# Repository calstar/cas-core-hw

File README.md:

# cas-core-hw
Common Avionics Stack - Core Module - Hardware

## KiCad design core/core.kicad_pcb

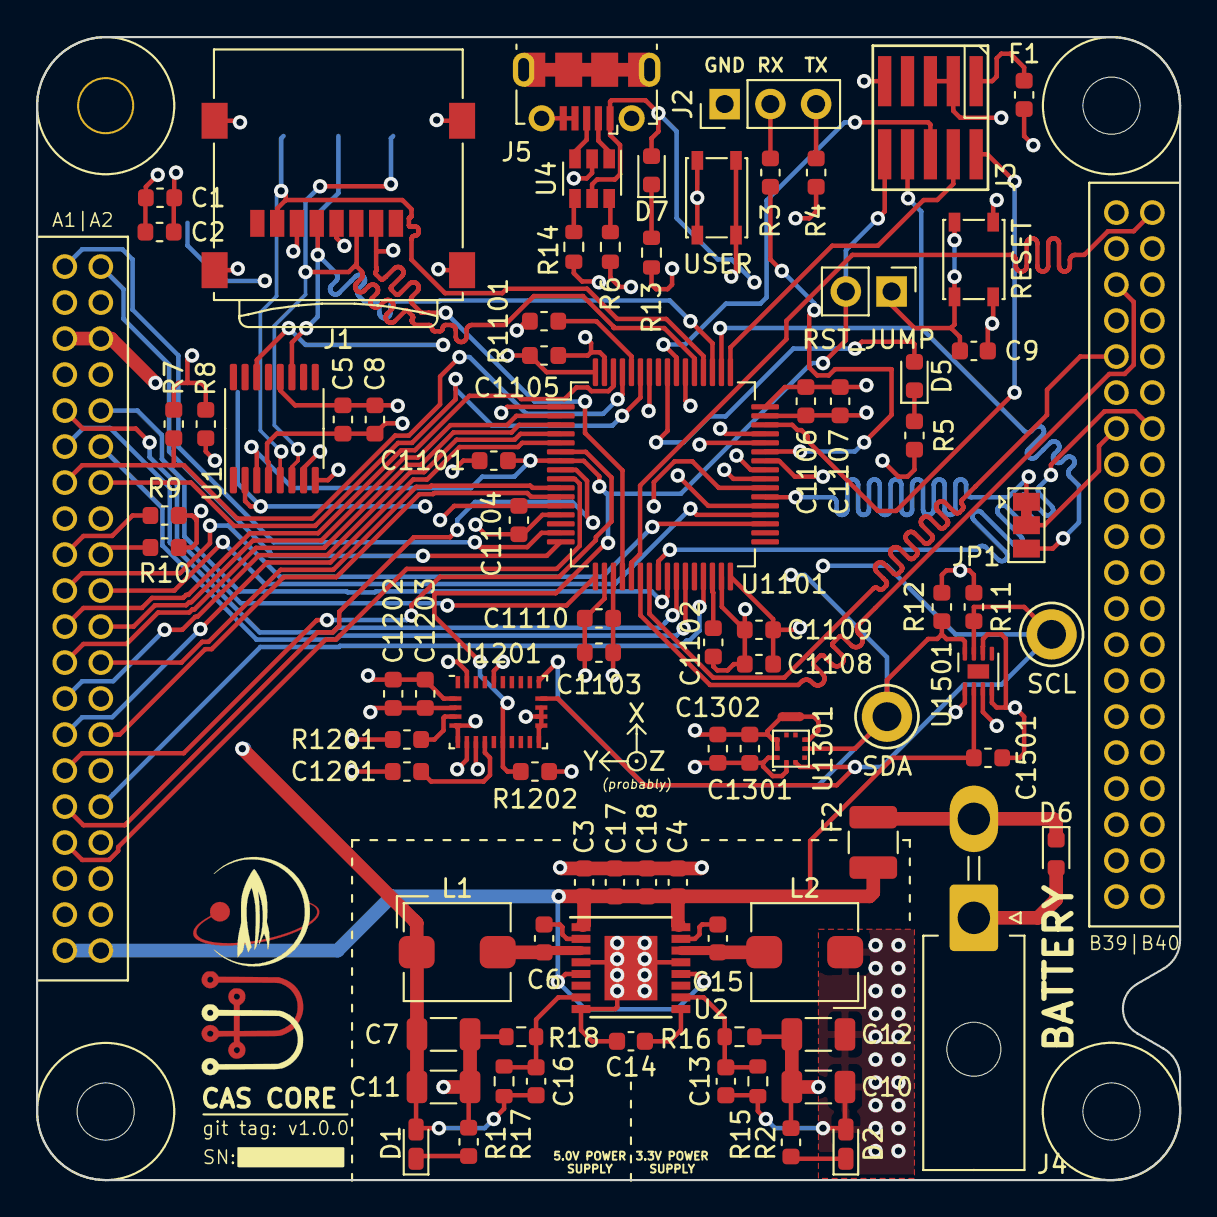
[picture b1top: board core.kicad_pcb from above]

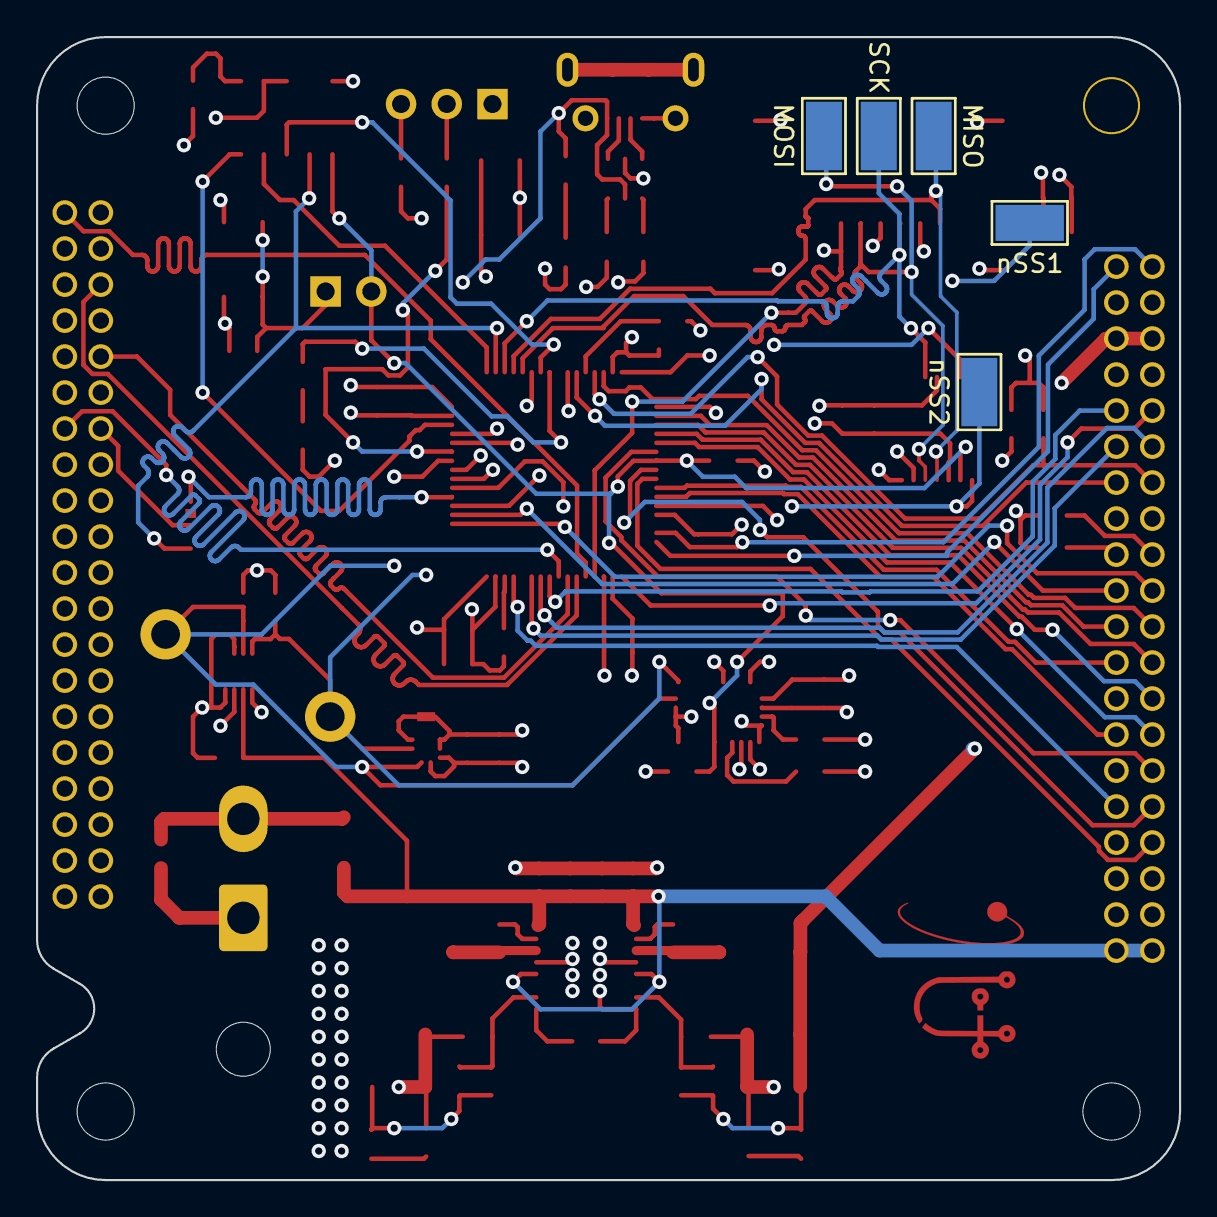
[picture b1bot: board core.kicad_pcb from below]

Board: 4 copper layers, 63.5 x 63.5 mm, 91 parts (5 on the bottom side), 78 nets.

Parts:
C1, C3, C4, C5, C1103: 10u; C_0603_1608Metric
C2, C6, C8, C9, C15: 100n; C_0603_1608Metric
C7, C10, C11, C12: 22u; C_1206_3216Metric
C13, C16: 10p; C_0603_1608Metric
C14, C1107: 1u; C_0603_1608Metric
C17, C18, C1101, C1104, C1105, C1106, C1108, C1109, C1110, C1501: 0.1u; C_0603_1608Metric
C1102: 4.7u; C_0603_1608Metric
C1201: 1uF; C_0603_1608Metric
C1202: 120nF; C_0603_1608Metric
C1203, C1301, C1302: 100nF; C_0603_1608Metric
D1, D2: LED; LED_0603_1608Metric_Castellated
D5, D7: LED; LED_0603_1608Metric
D6: 40V; D_0603_1608Metric
F1: Fuse_Small; Fuse_0603_1608Metric
F2: CHONK; Fuse_1210_3225Metric
H1: STAR; star_fancy
H2: BAC; bac
J1: Micro_SD_Card; microSD_HC_Wuerth_693072010801
J2: UART_DEBUG; PinHeader_1x03_P2.54mm_Vertical
J3: Conn_ARM_JTAG_SWD_10; FTSH-105-01-L-DV-K
J4: Conn_01x02; Molex_Mini-Fit_Jr_5569-02A2_2x01_P4.20mm_Horizontal
J5: USB_OTG; USB_Micro-B_Molex-105017-0001
J1001: CAS_stacking; CAS_physical
JP1: Jumper_3_Bridged12; SolderJumper-3_P1.3mm_Bridged12_Pad1.0x1.5mm
JP2: RST_JUMP; PinHeader_1x02_P2.54mm_Vertical
L1: 4.7u; L_Bourns_SRP5030T
L2: 2.2u; L_Bourns_SRP5030T
NT1301: Net-Tie_2; NetTie-2_SMD_Pad0.5mm
R1, R2, R5, R13: 1k; R_0603_1608Metric
R3, R4: 330; R_0603_1608Metric
R6, R14: 20; R_0603_1608Metric
R7, R8, R9, R10, R11, R12: 4.7k; R_0603_1608Metric
R15: 73.2k; R_0603_1608Metric
R16, R18: 22.1k; R_0603_1608Metric
R17: 124k; R_0603_1608Metric
R1101: 10K; R_0603_1608Metric
R1201, R1202: 10k; R_0603_1608Metric
SW1: RESET; SW_SPST_PTS810
SW2: USER; SW_SPST_PTS810
TP2: MISO; TestPoint_Keystone_5019_Minature
TP3: SCK; TestPoint_Keystone_5019_Minature
TP4: nSS2; TestPoint_Keystone_5019_Minature
TP6: SDA; TestPoint_Keystone_5010-5014_Multipurpose
TP8: MOSI; TestPoint_Keystone_5019_Minature
TP9: nSS1; TestPoint_Keystone_5019_Minature
TP12: SCL; TestPoint_Keystone_5010-5014_Multipurpose
U1: SC18IS600; TSSOP-16_4.4x5mm_P0.65mm
U2: TPS54X94; TSSOP-16-1EP_4.4x5mm_P0.65mm
U4: USBLC6-2SC6; SOT-23-6
U1101: STM32F401RETx; LQFP-64_10x10mm_P0.5mm
U1201: BNO055; LGA-28_5.2x3.8mm_P0.5mm
U1301: BMP388
U1501: MAX17049G+; TDFN-8-1EP_2x2mm_P0.5mm_EP0.8x1.2mm

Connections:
+3V3: C1.1, C2.1, C5.1, C8.1, C10.2, C12.2, C13.1, C1103.1, C1104.1, C1105.1, C1106.1, C1107.1, C1108.1, C1109.1, C1110.1, C1202.2, C1203.2, C1301.2, C1302.1, D2.2, F1.2, J1.4, J1001.A35, J1001.A36, L2.1, R7.1, R8.1, R9.1, R10.1, R11.1, R12.1, R15.1, R1201.2, R1202.2, SW2.1, U1.12, U1101.1, U1101.13, U1101.19, U1101.32, U1101.48, U1101.64, U1201.3, U1201.28, U1301.1, U1301.10, U1501.3
+5V: C7.2, C11.2, C16.1, D1.2, J1001.A5, J1001.A6, L1.1, R17.1
+BATT: C3.2, C4.2, C17.2, C18.2, C1501.1, F2.1, J1001.A39, J1001.A40, U2.1, U2.5, U2.12, U2.16, U1501.2
/FB1: C16.2, R17.2, R18.1, U2.7
/FB2: C13.2, R15.2, R16.1, U2.10
/I2C1_SCL: J1001.A13, R7.2, U1101.61
/I2C1_SDA: J1001.A14, R8.2, U1101.59
/I2C2_SCL: J1001.A17, R9.2, U1.8
/I2C2_SDA: J1001.A18, R10.2, U1.7
/I2C3_SCL: R11.2, TP12.1, U1101.41, U1201.19, U1301.2, U1501.7
/I2C3_SDA: R12.2, TP6.1, U1101.40, U1201.20, U1301.4, U1501.8
/INT1: J1001.A1, U1101.15
/INT2: J1001.A2, U1101.16
/INT3: J1001.A9, U1101.17
/INT4: J1001.A10, U1101.25
/INT5: J1001.A11, U1101.26
/INT6: J1001.A12, U1101.27
/INT7: J1001.A19, U1101.35
/INT8: J1001.A20, U1101.36
/INT_I2C: U1.14, U1101.37
/SPI2_MISO: J1001.A24, U1101.10
/SPI2_MOSI: J1001.A28, U1101.11
/SPI2_SCK: J1001.A32, U1101.29
/SPI2_nSS1: J1001.A21, U1101.62
/SPI2_nSS2: J1001.A22, U1101.2
/SPI2_nSS3: J1001.A23, U1101.3
/SPI2_nSS4: J1001.A25, U1101.4
/SPI2_nSS5: J1001.A27, U1101.5
/SPI2_nSS6: J1001.A29, U1101.6
/SPI2_nSS7: J1001.A31, U1101.8
/SPI2_nSS8: J1001.A33, U1101.9
/SPI3_MISO: J1.7, TP2.1, U1.5, U1101.52
/SPI3_MOSI: J1.3, TP8.1, U1.6, U1101.53
/SPI3_SCK: J1.5, TP3.1, U1.11, U1101.51
/SPI3_nSS1: J1.2, TP9.1, U1101.20
/SPI3_nSS2: TP4.1, U1.2, U1101.39
/SPIHS_MISO: J1001.B5, U1101.22
/SPIHS_MOSI: J1001.B9, U1101.23
/SPIHS_SCK: J1001.B2, U1101.21
/SPIHS_nSS1: J1001.B13, JP1.2
/SPIHS_nSS1soft: JP1.1, U1101.38
/SPIHS_nSS2: J1001.B14, U1101.24
/SW1: C6.1, L1.2, U2.3
/SW2: C15.2, L2.2, U2.14
/SWDCLK: J3.4, U1101.49
/SWDIO: J3.2, U1101.46
/SWO: J3.6, U1101.55
/TDI: J3.8, JP1.3, U1101.50
/UART_RX: R3.2, U1101.43
/UART_TX: R4.2, U1101.58
/USB_DM: R6.1, U1101.44
/USB_DM_I: J5.2, U4.1
/USB_DP: R14.2, U1101.45
/USB_DP_I: J5.3, U4.3
/USB_VBUS: D7.2, J5.1, U4.5, U1101.42
/USER_BUTTON: SW2.2, U1101.54
/USER_LED: D5.2, U1101.56
/nRESET: C1101.1, J3.10, JP2.2, R1202.1, U1.3, U1101.7, U1201.11
GND: C1.2, C2.2, C3.1, C4.1, C5.2, C7.1, C8.2, C9.2, C10.1, C11.1, C12.1, C14.2, C17.1, C18.1, C1101.2, C1102.2, C1103.2, C1104.2, C1105.2, C1106.2, C1107.2, C1108.2, C1109.2, C1110.2, C1201.1, C1202.1, C1203.1, C1301.1, C1302.2, C1501.2, D6.2, J1.6, J1.9, J2.1, J3.3, J3.5, J3.9, J4.1, J5.4, J5.5, J5.6, J1001.A3, J1001.A4, J1001.A7, J1001.A8, J1001.A15, J1001.A16, J1001.A26, J1001.A30, J1001.A34, J1001.A37, J1001.A38, J1001.B1, J1001.B3, J1001.B4, J1001.B6, J1001.B7, J1001.B8, J1001.B10, J1001.B11, J1001.B12, NT1301.2, R1.2, R2.2, R5.2, R13.2, R16.2, R18.2, R1101.2, SW1.1, U1.4, U2.4, U2.8, U2.13, U2.17, U4.2, U1101.12, U1101.18, U1101.31, U1101.47, U1101.63, U1201.2, U1201.5, U1201.6, U1201.15, U1201.16, U1201.17, U1201.18, U1201.25, U1301.8, U1301.9, U1501.1, U1501.4, U1501.6
unnamed: C6.2, U2.2
unnamed: C9.1, JP2.1, SW1.2
unnamed: C14.1, U2.9
unnamed: C15.1, U2.15
unnamed: C1102.1, U1101.30
unnamed: C1201.2, U1201.9
unnamed: D1.1, R1.1
unnamed: D2.1, R2.1
unnamed: D5.1, R5.1
unnamed: D6.1, F2.2, J4.2
unnamed: D7.1, R13.1
unnamed: F1.1, J3.1
unnamed: J2.2, R3.1
unnamed: J2.3, R4.1
unnamed: NT1301.1, U1301.5
unnamed: R6.2, U4.6
unnamed: R14.1, U4.4
unnamed: R1101.1, U1101.60
unnamed: R1201.1, U1201.4

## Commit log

2020-06-27 Backlink to CADLAB.io has been added.
2020-10-28 add basic schematic
2020-10-28 fix borked submodule
2020-10-29 Ready CAS for review
2020-10-29 fix footprint association
2020-10-29 fix usb connector
2020-11-09 Update block schematics and layout
2020-11-10 Done layout
2020-11-16 Address comments
2020-11-20 Fix Battery Connector's Direction
2020-11-28 fix connector (again)
2020-11-30 update layout
2020-11-30 Second Layout pass on core
2021-01-09 update schematic
2021-01-09 made layout revisions
2021-01-09 update silk
2021-01-12 fix hardware schematic blocks
2021-01-12 fix silk
2021-01-12 New regulator
2021-01-13 Add more artwork
2021-01-15 Bump rev
2021-03-02 add core fun bom
